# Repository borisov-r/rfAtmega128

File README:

Simple PCB with ATmega128RFa1 processor and usb. 
Main application of this board will be in our RepRap projects.

This work is licensed under the GNU GPL v3 or (at the user's discretion) any later version.
Software that will be used in this project is completely free and should be licensed under GPL v2 or later.

As a pins and code reference I'll use zigduino project:
http://www.logos-electro.com/zigduino/

============================================================================

Components:
1. ATmega128RFa1 -> 64 pins QFN @ 3.3 V
2. FT232RL       -> 28 pins     @ 3.3 V
3. BA033         -> 5 pins      @ -0.3 - 35 V
4. 2450FB15L0001 -> 6 pins      - RF balun
5. MCP809T-270I/TT -> added to RESET pin for programming
6. tunning capacitors -> 22 pF, 0.5 - 1.5 pF, 0603
7. RPSMA connector or PCB antenna
8. ICSP connector

============================================================================

Basic processes of the foundries should be examined and compared, so a simplified
trasistor model could be generated for more universal design.

Other option is a model to be generated according the needs and after that the most
suitable foundry should be chosen.

============================================================================

Schematic and layout design will be done using KiCAD.
Eventually a 3D models of the components will be added to the PCB.

============================================================================

Additional software for testing should be implemented.

Main RF libraries:
http://www.nongnu.org/uracoli/
http://freaklabs.org/index.php/chibiArduino.html
http://www.contiki-os.org
https://github.com/erictj/uracoli/tree/master/wibo
https://github.com/maniacbug/contiki-avr-zigduino
http://code.google.com/p/looci/wiki/GettingStartedContikiAVRRaven

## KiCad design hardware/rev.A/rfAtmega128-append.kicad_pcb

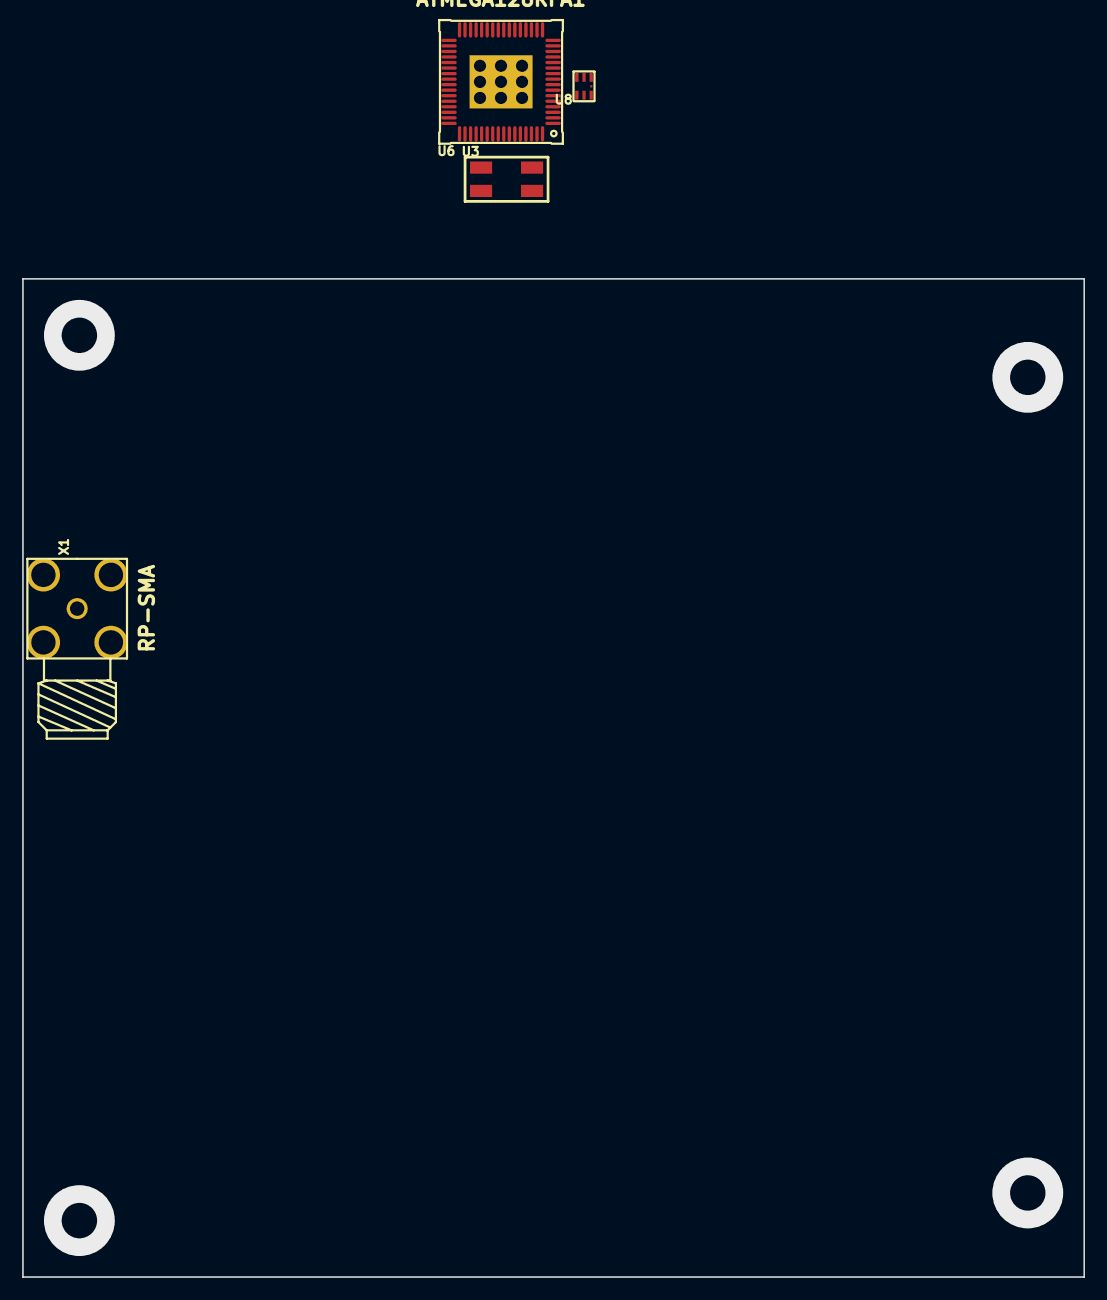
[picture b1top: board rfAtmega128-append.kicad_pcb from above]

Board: 2 copper layers, 95.9 x 90.2 mm, 4 parts (0 on the bottom side), 6 nets, no tracks yet.

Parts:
U3: Q16.000; crystal_xg6x3p5
U6: ATMEGA128RFA1; atmega128rfa1
U8: 2450FB15L0001
X1: RP-SMA; rp-sma

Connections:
/gnd: U3.2, U3.4, U6.7, U6.10, U6.11, U6.20, U6.24, U6.35, U6.45, U6.55, U6.58, U6.61, U6.65, U8.5, U8.6
/pwr_atmega: U6.21, U6.22, U6.23, U6.33, U6.34, U6.44, U6.54, U6.59
unnamed: U3.1, U6.56
unnamed: U6.8, U8.4
unnamed: U6.9, U8.3
unnamed: U3.3, U6.57

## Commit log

2012-04-02 added more readme files
2012-04-03 added initial library with atmega128rfa1, r, l, c - 0603
2012-04-03 added TANT_CAP_0603 to library
2012-04-04 ft232rl added to library
2012-04-10 Added many components to schematic library and schematic changed.
2012-04-17 modified components from schematic library and schematic optimized.
2012-04-17 Changed README_HARDWARE in hardware directory. Should be improved later.
2012-04-18 Added arduino kicad reference project, schematic almost finished, board layout.
2012-04-19 Added pcb libraries and 3d models for the PCB. Added to some components in schematic datasheets and footprints.
2012-04-20 Schmatics is more readable now and added most of the modules to the components with references.
2012-04-23 Changes in schematic, board is modified and some lib files updated.
2012-04-26 Netlist and components list generated.
2012-05-17 Added test board to the project and the initial netlist.
2012-05-18 Old hardware design is now moved to folder v001 and new design is started in dev folder
2012-05-21 New schematic to finish at home.
2012-05-22 dev board schematic is finished now. Need to add modules of few resistors and condensators.
2012-05-23 Initial pcb board layout started.
2012-05-28 Board routing started and rf part done.
2012-05-31 Most of ATmega128rfA1 pins are connected now. Additional power connector should be added with 2.54 mm stepping near to digital pins.
2012-06-04 Removed test pads, atmega connectors are routed. FTDI connector needs routing.
2012-06-05 board routed. size needs more precission and zone (copper pour) needs review.
2012-06-06 Layout ready, needs 2 drills for mounting and copper pour (zones in kicad).
2012-06-06 Board is finished. Need to add grounding viases in RF part and some texts.
2012-06-07 Added RF viases, all viases are now 7 types. Generated gerber files and drills in production directory. All need review before sending for production.
2012-06-08 Viases circles from comments layer moved to silkscreen layer. Drills exported in .drl file.
2012-06-11 Board changed to be manufactured at iteadstudio.com. Added bottom SilkScreen and rfAtmega128china.brd.
2012-06-12 Added zip file sended for manufacturing.
2012-06-12 Directory structure changed in hardware. Board is now called rfAtmega128 rev.A and is send for manufacturing.
2012-07-16 Added BOM of the board and fixed some resistor values in the schematic.
2012-07-18 Changed D1 to 1N4007 in the schematic.
2012-07-18 Modified BOM to use 1N4007 as a diode.
2012-07-20 Pins swapped of the RX and TX protective diodes marked on schematic. Resistor values of R6 and R7 changed to 0 in BOM and netlist.
2012-07-26 Added RF software libraries link to README
2012-07-26 Added chibiArduino link to README
2012-09-24 Added schematic in pdf format and pins explained on layout.
2012-10-15 Added to firmware directory testCapSensor and agilartTest.
2012-10-26 Added some documentation files and updated schematic.
2012-10-26 Added MISO, MOSI, SCK pins to image layout.
2013-01-02 Some small updates.
2013-01-05 Arduino IDE working and all DIO verified.
2013-01-05 All PWM working. ADC doesn't work yet.
2013-01-06 remove deprecated typedef avr-libc v1.8.0 more info in issue: https://github.com/arduino/Arduino/issues/795
2013-01-06 patch analogRead in wiring_analog.c and now all analog pins works fine
2013-01-07 Updated productionFiles for easier mounting of the components.
2013-01-07 add explanatory information about pins in pins_arduino.h
2013-01-09 Bug in the firmware, ATmegaBOOT_168_atmega128rfa1.hex and .elf were .html files and now they are intel hex format.
2013-09-01 Added Zigduino Radio Examples, CW and Spectrum analyzer
